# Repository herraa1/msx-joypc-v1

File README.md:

# PC gameport joystick controller adapter for MSX (msx-joypc) v1

Connect [PC gameport joysticks](https://en.wikipedia.org/wiki/Game_port) to [MSX computers](https://www.msx.org/wiki/).

> [!NOTE]
>
> No build instructions are yet provided, but if you are brave enough go for the [recommended build](#recommended-build).
>

## Introduction

The msx-joypc v1 is an adapter that allows connecting PC gameport joysticks to [MSX general purpose I/O ports](https://www.msx.org/wiki/General_Purpose_port).

The main features of the msx-joypc v1 adapter are:
* small footprint
* made of widely available electronic components
* behaves as a cord extension between the MSX computer and the PC gameport joystick
* uses a female standard DE9 connector on the adapter's MSX joystick side
* uses a [DA-15](https://en.wikipedia.org/wiki/D-subminiature) socket on the adapter's PC gameport joystick side
* no need for external power supply, the adapter draws current from the MSX port
* low power consumption (<20mA)
* serial debug provides information about the operation of the adapter

## [Hardware](hardware/kicad/)

The msx-joypc v1 adapter uses an [Atmega328p](https://en.wikipedia.org/wiki/ATmega328) to convert the [PC gameport joystick signalling](https://www.epanorama.net/documents/joystick/pc_joystick.html) to the [MSX joystick standard signalling](https://www.msx.org/wiki/Joystick_control).

A two-sided printed circuit board (PCB) is used to put together all components:
* An Atmega328p as the main MCU, running at 5V 16MHz
* Two 74LS03 quad 2-input NAND gates with open collectors to completely mimic the standard MSX joystick behavior
* A PTC fuse to minimize damage to the MSX computer in case something goes wrong with the board
* Several additional required components (crystal, diode, leds, resistors, ceramic capacitors and a tantalum capacitor)
* An angled DA-15 socket is used to directly connect the PC gameport joystick
* A PH2.0 connector is used to connect the MSX cable extension
* A 2.54 pitch debug header is added for serial debug and programming
* An ICSP header is provided for burning a bootloader or to flash the chip using a hardware programmer
* A DIP switch to configure the adapter for compatibility with different PC joysticks

Connection to the MSX general purpose I/O port is implemented using a DE9 joystick extension cable with a female DE9 connector on one side and a loose end on the other side.
The MSX joystick extension cable loose end is wired according to the following pinout mapping.

|  |
|:--|
| MSX joystick connector pinout, from controller plug side |

| MSX side pin | Cable color (may vary) | Signal |
| ------------ | ---------------------- | ------ |
| 5            | Brown                  | +5v    |
| 4            | Orange                 | RIGHT  |
| 3            | Grey                   | LEFT   |
| 2            | Black                  | DOWN   |
| 1            | Red                    | UP     |
| 6            | Green                  | TRIGA  |
| 7            | White                  | TRIGB  |
| 8            | Blue                   | OUT    |
| 9            | Yellow                 | GND    |

The msx-joypc v1 is fully compatible with MSX joysticks and honors the pin8 (OUT) signal.

The adapter uses open collector outputs (using 74LS03 Quad 2-Input NAND gates with open collector outputs) which makes the adapter safer [^2] than the
standard MSX joystick schematic depicted in the MSX Technical Data Book, as it avoids a series of undesired conditions that can lead to bus contention/short circuits.

Power is drawn from the +5V signal of the MSX general purpose I/O port, which is capable of delivering up to 50mA [^1].
The msx-joypc v1 draws below 20mA from the port when a controller is connected, so it is on the safe side. Anyway, the msx-joypc adapter uses a Positive Temperature Coeficient (PTC) resettable fuse of 50mA (F1) to limit current in case something goes wrong.

Also on the power side, a [1N5819 Schottky diode](https://www.diodes.com/assets/Datasheets/1N5819HW.pdf) (D1) is used to avoid leaking current from the msx-joypc adapter to the MSX in case power is applied to one of the VCC pins available on the ICSP or Debug headers while the adapter is plugged into an MSX.

Connection to the PC gameport joystick is done via a PC gameport joystick socket.

|  |
|:--|
| Gameport connector pinout, from PC gameport joystick side |

| Gameport pin   | Signal       | Comment                                                                   |
| -------------- | -------------| ------------------------------------------------------------------------- |
| 1              | +5V          | +5V power                                                                 |
| 2              | B1           | Button1                                                                   |
| 3              | X1           | Joystick 1 - X axis                                                       |
| 4              | GND          | ground                                                                    |
| 5              | GND          | ground                                                                    |
| 6              | Y1           | Joystick 1 - Y axis                                                       |
| 7              | B2           | Button2                                                                   |
| 8              | +5V          | +5V power                                                                 |
| 9              | +5V          | +5V power                                                                 |
| 10             | B3           | Button3                                                                   |
| 11             | X2           | Joystick 2 - X axis                                                       |
| 12             | GND/MIDI_OUT | ground / MIDI out                                                         |
| 13             | Y2           | Joystick 2 - Y axis                                                       |
| 14             | B4           | Button4                                                                   |
| 15             | +5V/MIDI_IN  | +5V power / MIDI_IN                                                       |

The PC gameport joystick uses 5V for power and logic.

Power for the PC gameport joystick is provided by the MSX +5V rail.

### Recommended Build

Please, use [msx-joypc-v1 Build2](#build2) for making new boards.

### [Build2](hardware/kicad/msx-joypc-v1-build2)

[Bill Of Materials (BoM)](https://html-preview.github.io/?url=https://raw.githubusercontent.com/herraa1/msx-joypc-v1/main/hardware/kicad/msx-joypc-v1-build2/bom/ibom.html)

This build fixes the following errata:
- make the ICSP header work again
- add (optional) RN1 and RN2 4k7 pull-downs to joystick signals to avoid spurious button joystick actions while powering up

This board has been successfully built and works fine.

### Build1

> [!WARNING]
> This build is broken. I messed up the ICSP header after a last-minute pin reordering. Meh.
> It can be fixed by cutting two traces, exposing two traces and using a pair of jumper wires to bridge the necessary points.
>
> Do NOT build. Use the [recommended build](#recommended-build) instead.
>

## [Firmware](firmware/msx-joypc-v1/)

The msx-joypc v1 adapter firmware uses a slightly modified version of [Necroware's GamePort adapter firmware](https://github.com/necroware/gameport-adapter) to read the PC gameport joystick status.

The following elements are used as inputs:
* joystick X and Y axis as direction arrows
* button 1, as Trigger 1
* button 2, as Trigger 2

Those elements' status are processed by the msx-joypc firmware and transformed into MSX general purpose I/O port's signals on the fly.

## [Enclosure](enclosure/)

### Acrylic

A simple acrylic enclosure design for the project is provided to protect the electronic components and provide strain relief for the extension cord.

The enclosure uses a 3mm acrylic sheet.

## Configuration Switches

Joystick Model               | Buttons | Axes  |  Hat | SW1-4 | Protocol   | Comments
-----------------------------|---------|-------|------|-------|------------|------------------------------------
Generic Analog               | 2       | 2     | 0    | 0000  | Analogue   |
Generic Analog               | 4       | 2     | 0    | 1000  | Analogue   |
Generic Analog               | 4       | 3     | 0    | 0100  | Analogue   | 3rd Axis is throttle
Generic Analog               | 4       | 4     | 0    | 1100  | Analogue   |
CH FlightStick               | 4       | 4     | 1    | 0010  | Analogue   |
CH F16 Combat Stick          | 10      | 3     | 1    | 0110  | Analogue   |
ThrustMaster                 | 4       | 3     | 1    | 1010  | Analogue   |
Sidewinder GamePad           | 10      | 2     | 0    | 1110  | Sidewinder |
Sidewinder 3D Pro            | 8       | 4     | 1    | 1110  | Sidewinder |
Sidewinder 3D Pro Plus       | 9       | 4     | 1    | 1110  | Sidewinder | First version of Precision Pro
Sidewinder Precision Pro     | 9       | 4     | 1    | 1110  | Sidewinder |
Sidewinder FFB Pro           | 9       | 4     | 1    | 1110  | Sidewinder | FFB not yet implemented
Sidewinder FFB Wheel         | 8       | 3     | 0    | 1110  | Sidewinder | FFB not yet implemented
Gravis GamePad Pro           | 10      | 2     | 0    | 0001  | GrIP       |
Logitech WingMan Extreme     | 6       | 3     | 1    | 1001  | ADI        |
Logitech CyberMan 2          | 8       | 6     | 0    | 1001  | ADI        |
Logitech WingMan Interceptor | 9       | 3     | 3    | 1001  | ADI        | 2 hats are mapped as 4 axes
Logitech ThunderPad Digital  | 8       | 2     | 0    | 1001  | ADI        | Directional buttons mapped as 2 axes
Logitech WingMan Gamepad     | 11      | 2     | 0    | 1001  | ADI        | Directional buttons mapped as 2 axes
Logitech WingMan Light       | 2       | 2     | 0    | 0000  | Analogue   |

For an up to date information see [Which joysticks does this adapter support](https://github.com/necroware/gameport-adapter?tab=readme-ov-file#which-joysticks-does-this-adapter-support) on [Necroware's GamePort adapter project](https://github.com/necroware/gameport-adapter).

## LED indicators

| **LED**   | **State**      | **Indication** |
|-----------|----------------|---------------|
| _POWER_   | Off            | board is not receiving 5V power |
| _POWER_   | Solid Red      | board is receiving 5V power     |
| _JoyPort_ | Off            | no PC joystick connected or recognized |
| _JoyPort_ | Solid Green    | PC joystick connected and ready to use |

## References

MSX general purpose I/O port
* https://www.msx.org/wiki/General_Purpose_port

Atmega328p pinout
- https://camo.githubusercontent.com/06bc0a6bb71729956af107f56c3e57bd065d9fb924bcc7f6bb8fbb487a1a5e55/68747470733a2f2f692e696d6775722e636f6d2f6e6177657145362e6a7067

Joystick PC Gameport pinout
* https://allpinouts.org/pinouts/connectors/input_device/joystick-pc-gameport/

PC joystick interface
* https://www.epanorama.net/documents/joystick/pc_joystick.html

Necroware's GamePort adapter project
* https://github.com/necroware/gameport-adapter

Using a PC Joystick with the Arduino
* http://www.built-to-spec.com/blog/2009/09/10/using-a-pc-joystick-with-the-arduino/

Arduino gameport interface
* https://build-its.blogspot.com/2012/01/arduino-game-port-interface.html

DIY gameport to USB adapter
* https://littlebigtech.net/posts/diy-gameport-to-usb-adapter/

## Image Sources

* https://www.oshwa.org/open-source-hardware-logo/
* https://en.wikipedia.org/wiki/File:Numbered_DE9_Diagram.svg

[^1]: https://www.msx.org/wiki/General_Purpose_port
[^2]: https://www.msx.org/wiki/Joystick/joypad_controller (see "Undesired Conditions")

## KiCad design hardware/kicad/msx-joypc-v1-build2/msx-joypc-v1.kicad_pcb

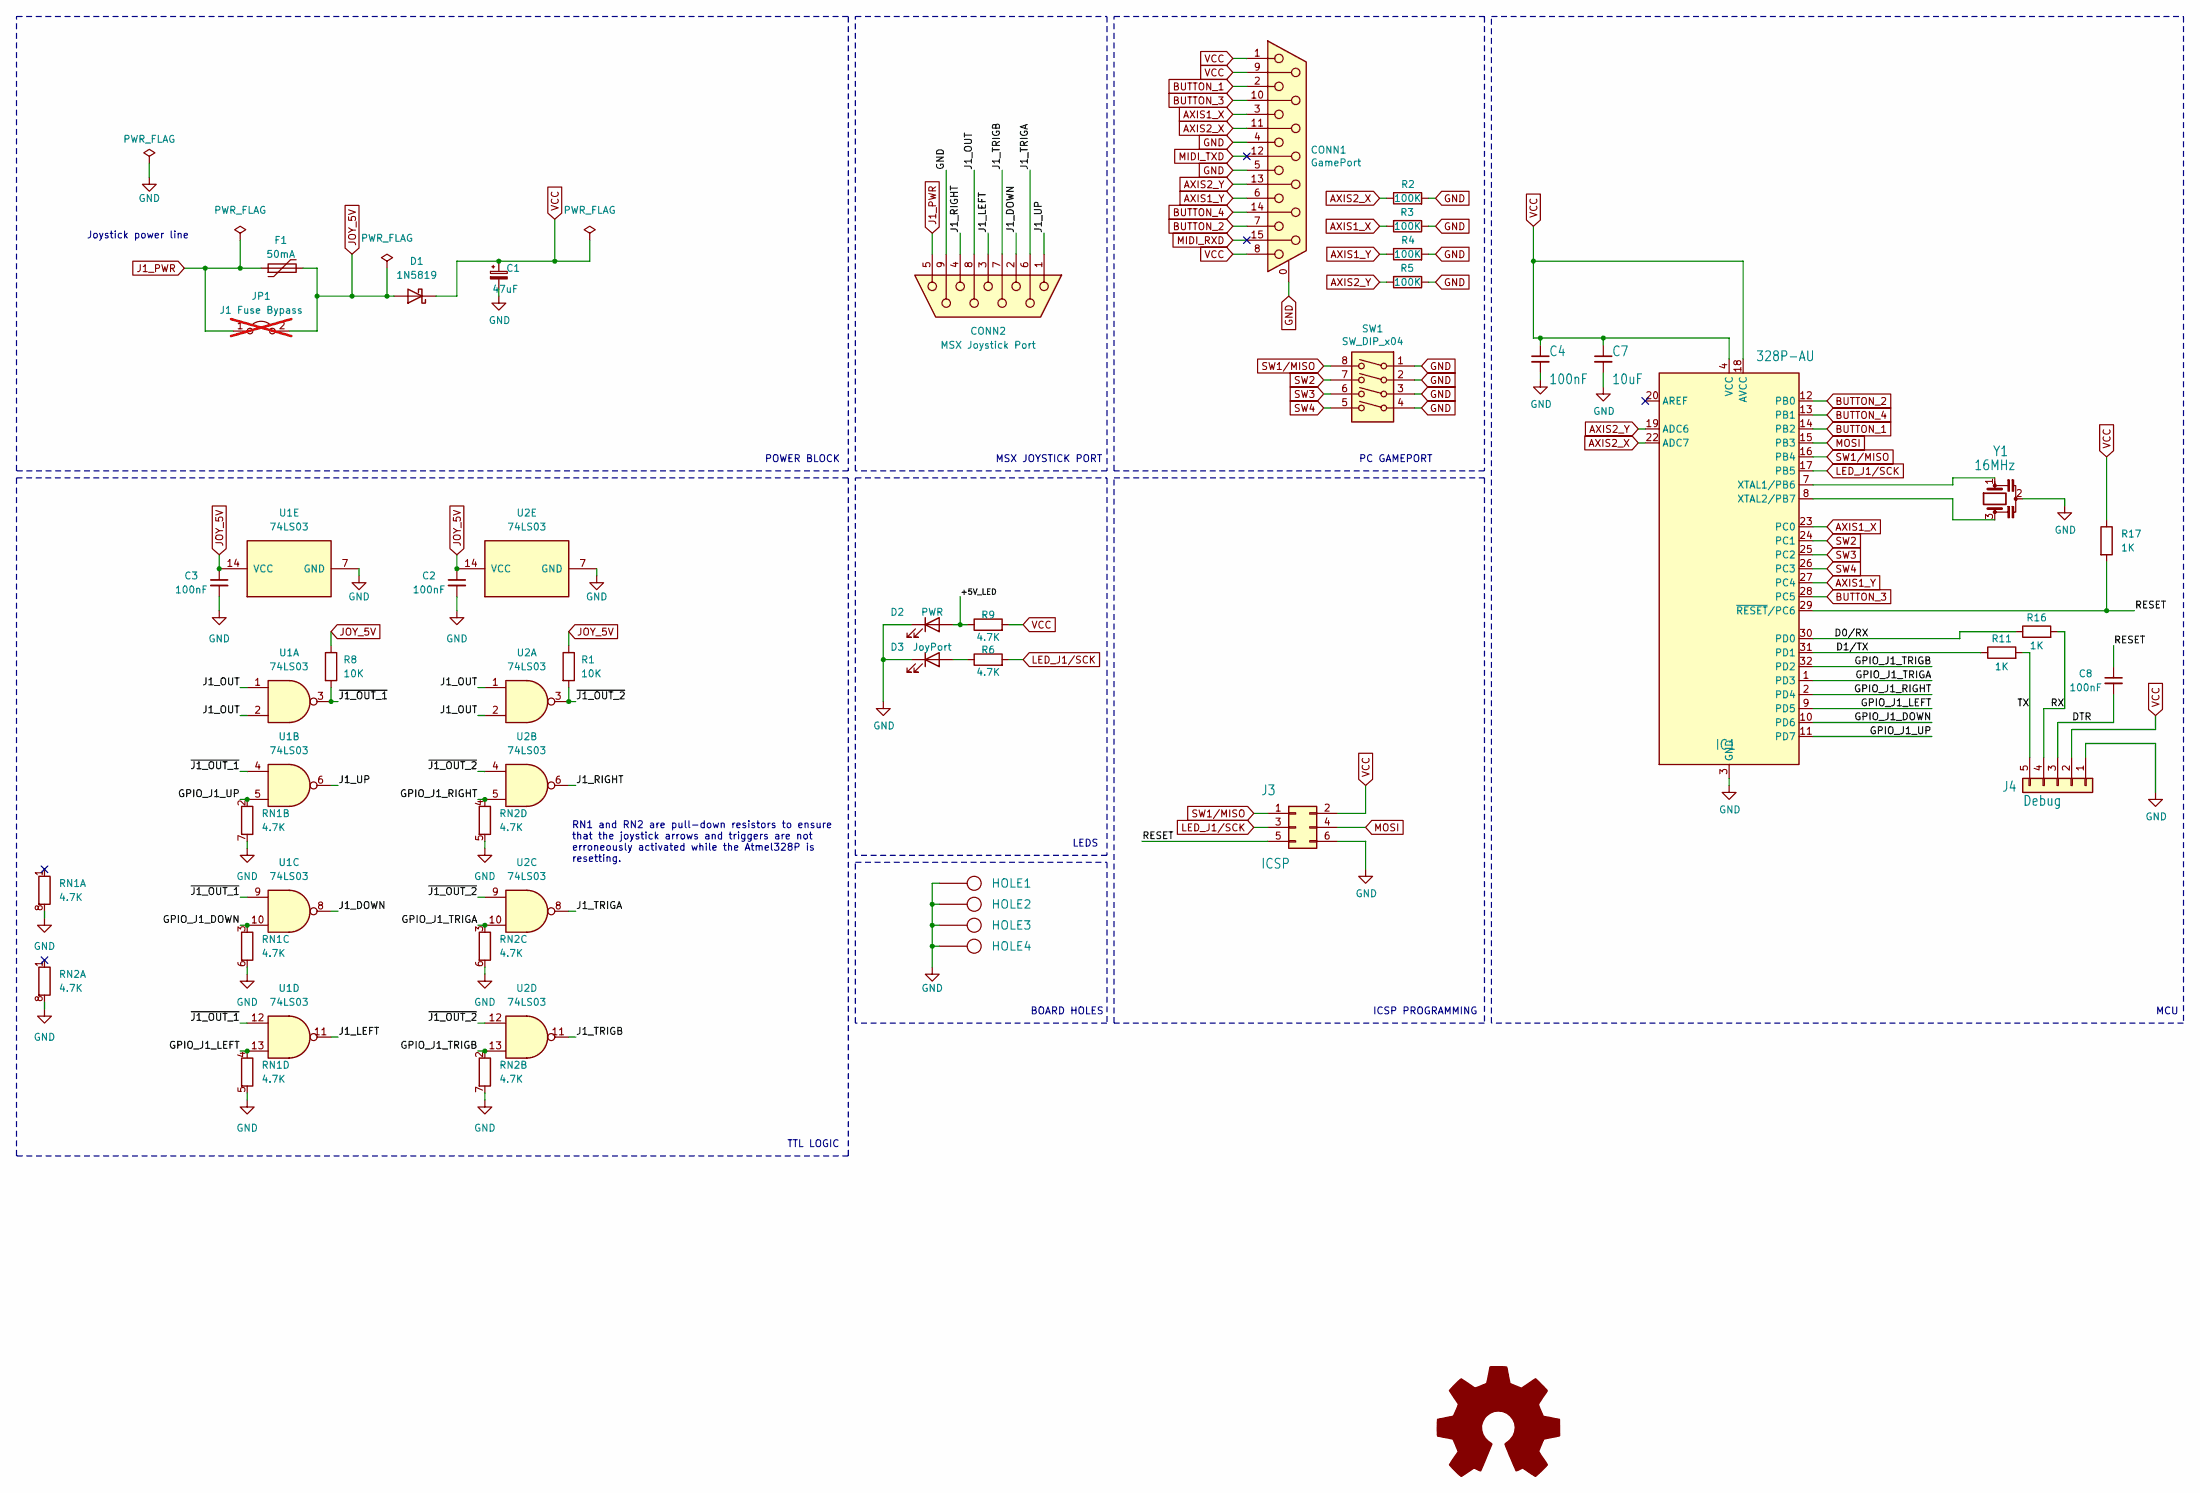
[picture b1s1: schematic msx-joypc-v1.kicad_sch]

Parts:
C1: 47uF; CP_EIA-3216-18_Kemet-A_Pad1.58x1.35mm_HandSolder
C2, C3, C4, C8: 100nF; C_0805_2012Metric_Pad1.18x1.45mm_HandSolder
C7: 10uF; C_0805_2012Metric_Pad1.18x1.45mm_HandSolder
CONN1: GamePort; DSUB-15_Female_Horizontal_P2.77x2.84mm_EdgePinOffset7.70mm_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; LCSC C77835
CONN2: MSX Joystick Port; JST_PH_B9B-PH-K_1x09_P2.00mm_Vertical
D1: 1N5819; D_SOD-123
D2: PWR; LED_0805_2012Metric_Pad1.15x1.40mm_HandSolder
D3: JoyPort; LED_0805_2012Metric_Pad1.15x1.40mm_HandSolder
F1: 50mA; Fuse_1206_3216Metric_Pad1.42x1.75mm_HandSolder
HOLE1, HOLE2, HOLE3, HOLE4: HOLE; Hole_3mm
IC1: 328P-AU; TQFP-32_7x7mm_P0.8mm
J3: ICSP; PinHeader_2x03_P2.54mm_Vertical
J4: Debug; PinHeader_1x05_P2.54mm_Vertical
JP1: J1 Fuse Bypass; PinHeader_1x02_P2.54mm_Vertical; not fitted
R1, R8: 10K; R_0805_2012Metric_Pad1.20x1.40mm_HandSolder
R2, R3, R4, R5: 100K; R_0805_2012Metric_Pad1.20x1.40mm_HandSolder; LCSC C172965
R6: 4.7K; R_0805_2012Metric_Pad1.20x1.40mm_HandSolder; LCSC C4310
R9: 4.7K; R_0805_2012Metric_Pad1.20x1.40mm_HandSolder
R11, R16, R17: 1K; R_0805_2012Metric_Pad1.20x1.40mm_HandSolder
RN1, RN2: 4.7K; R_Array_Concave_4x0603
SW1: SW_DIP_x04; SW_DIP_SPSTx04_Piano_10.8x11.72mm_W7.62mm_P2.54mm; LCSC C15781
SYM1: Logo_Open_Hardware_Large; OSHW-Logo_7.5x8mm_SilkScreen
U1, U2: 74LS03; SOIC-14_3.9x8.7mm_P1.27mm
Y1: 16MHz; Resonator_SMD_Murata_CSTxExxV-3Pin_3.0x1.1mm_HandSoldering

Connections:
/+5V_LED: D2.2 (A), R9.1
/D0/RX: IC1.30 (PD0), R16.1
/D1/TX: IC1.31 (PD1), R11.1
/DTR: C8.2, J4.3
/GPIO_J1_DOWN: IC1.10 (PD6), RN1.3 (R3.1), U1.10
/GPIO_J1_LEFT: IC1.9 (PD5), RN1.4 (R4.1), U1.13
/GPIO_J1_RIGHT: IC1.2 (PD4), RN2.4 (R4.1), U2.5
/GPIO_J1_TRIGA: IC1.1 (PD3), RN2.3 (R3.1), U2.10
/GPIO_J1_TRIGB: IC1.32 (PD2), RN2.2 (R2.1), U2.13
/GPIO_J1_UP: IC1.11 (PD7), RN1.2 (R2.1), U1.5
/J1_DOWN: CONN2.2, U1.8
/J1_LEFT: CONN2.3, U1.11
/J1_OUT: CONN2.8, U1.1, U1.2, U2.1, U2.2
/J1_RIGHT: CONN2.4, U2.6
/J1_TRIGA: CONN2.6, U2.8
/J1_TRIGB: CONN2.7, U2.11
/J1_UP: CONN2.1, U1.6
/RESET: C8.1, IC1.29 (~RESET/PC6), J3.5, R17.2
/RX: J4.4, R16.2
/TX: J4.5, R11.2
/~J1_OUT_1: R8.2, U1.3, U1.4, U1.9, U1.12
/~J1_OUT_2: R1.2, U2.3, U2.4, U2.9, U2.12
AXIS1_X: CONN1.3, IC1.23 (PC0), R3.2
AXIS1_Y: CONN1.6, IC1.27 (PC4), R4.1
AXIS2_X: CONN1.11 (P111), IC1.22 (ADC7), R2.1
AXIS2_Y: CONN1.13, IC1.19 (ADC6), R5.2
BUTTON_1: CONN1.2, IC1.14 (PB2)
BUTTON_2: CONN1.7, IC1.12 (PB0)
BUTTON_3: CONN1.10, IC1.28 (PC5)
BUTTON_4: CONN1.14, IC1.13 (PB1)
GND: C1.2, C2.2, C3.2, C4.2, C7.2, CONN1.0 (PAD), CONN1.4, CONN1.5, CONN2.9, D2.1 (K), D3.1 (K), HOLE1.1, HOLE2.1, HOLE3.1, HOLE4.1, IC1.3 (GND), IC1.5 (GND), IC1.21 (GND), J3.6, J4.1, R2.2, R3.1, R4.2, R5.1, RN1.5 (R4.2), RN1.6 (R3.2), RN1.7 (R2.2), RN1.8 (R1.2), RN2.5 (R4.2), RN2.6 (R3.2), RN2.7 (R2.2), RN2.8 (R1.2), SW1.1, SW1.2, SW1.3, SW1.4, U1.7 (GND), U2.7 (GND), Y1.2
J1_PWR: CONN2.5, F1.1, JP1.1 (A)
JOY_5V: C2.1, C3.1, D1.2 (A), F1.2, JP1.2 (B), R1.1, R8.1, U1.14 (VCC), U2.14 (VCC)
LED_J1/SCK: IC1.17 (PB5), J3.3, R6.2
MIDI_RXD: CONN1.15
MIDI_TXD: CONN1.12
MOSI: IC1.15 (PB3), J3.4
unnamed: D3.2 (A), R6.1
unnamed: IC1.7 (XTAL1/PB6), Y1.1
unnamed: IC1.8 (XTAL2/PB7), Y1.3
SW1/MISO: IC1.16 (PB4), J3.1, SW1.8
SW2: IC1.24 (PC1), SW1.7
SW3: IC1.25 (PC2), SW1.6
SW4: IC1.26 (PC3), SW1.5
VCC: C1.1, C4.1, C7.1, CONN1.1, CONN1.8, CONN1.9, D1.1 (K), IC1.4 (VCC), IC1.6 (VCC), IC1.18 (AVCC), J3.2, J4.2, R9.2, R17.1

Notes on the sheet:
MCU
LEDS
MSX JOYSTICK PORT
TTL LOGIC
BOARD HOLES
Joystick power line
ICSP PROGRAMMING
RN1 and RN2 are pull-down resistors to ensure that the joystick arrows and triggers are not erroneously activated while the Atmel328P is resetting.
PC GAMEPORT
POWER BLOCK

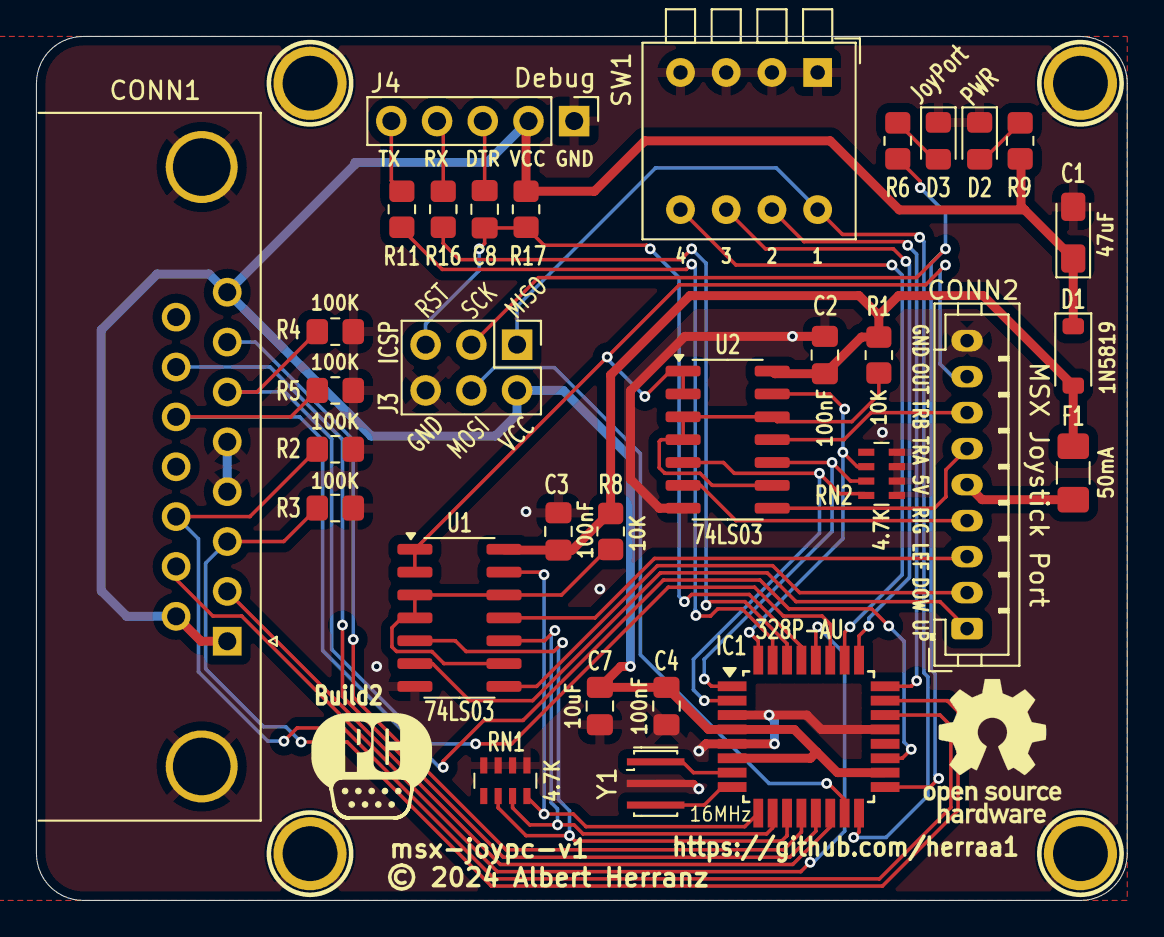
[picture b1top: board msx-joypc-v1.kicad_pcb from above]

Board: 2 copper layers, 60.6 x 48.0 mm, 37 parts (0 on the bottom side), 43 nets.

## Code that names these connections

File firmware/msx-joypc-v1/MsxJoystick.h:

/*
 * msx-joypc v1, a PC gameport to MSX joystick adapter
 * Copyright (C) 2024 Albert Herranz
 *
 * This code is released under GPL V2.0
 *
 * Valid-License-Identifier: GPL-2.0-only
 * SPDX-URL: https://spdx.org/licenses/GPL-2.0-only.html
 *
 */
//
// Based on Necroware's GamePort adapter firmware.
// Copyright (C) 2021 Necroware
//
// This program is free software: you can redistribute it and/or modify
// it under the terms of the GNU General Public License as published by
// the Free Software Foundation, either version 3 of the License, or
// (at your option) any later version.
//
// This program is distributed in the hope that it will be useful,
// but WITHOUT ANY WARRANTY; without even the implied warranty of
// MERCHANTABILITY or FITNESS FOR A PARTICULAR PURPOSE.  See the
// GNU General Public License for more details.
//
// You should have received a copy of the GNU General Public License
// along with this program. If not, see <https://www.gnu.org/licenses/>.

#pragma once

#include "Buffer.h"
#include "Joystick.h"
#include "Utilities.h"
#include <Arduino.h>

#include "DigitalPin.h"
#include <avr/wdt.h>

void __force_system_reset(void) {
	MCUSR = 0;
	wdt_enable(WDTO_250MS);
	while(1)  ;  // force WDT to reset system
}

class MsxJoystick {
public:
  bool init(Joystick *joystick) {
    
    if (!joystick || !joystick->init()) {
      return false;
    }

    m_joystick = joystick;
    m_state = State::BOOT_CONNECTED_CONNECTED;
    m_led.setHigh();

    const auto &desc = m_joystick->getDescription();
    log("Configured device: %s (%d axes, %d buttons)", desc.name, desc.numAxes, desc.numButtons);

    return true;
  }

  bool update() {
    if (!m_joystick || !m_joystick->update()) {
      return false;
    }

    const auto &state = m_joystick->getState();
    const auto &desc = m_joystick->getDescription();

#ifdef DIAG
    static auto last_state = m_joystick->getState();

    for (auto i = 0u; i < desc.numAxes; i++) {
        log_nolf("axes[%d] = %d,", i, state.axes[i]);
    }

    if (desc.hasHat) {
      if (last_state.hat != state.hat) {
        log_nolf("hat = %d,", state.hat);
      }
    }

    if (desc.numButtons) {
      if (last_state.buttons != state.buttons) {
        log_nolf("buttons = %d", state.buttons);
      }
    }
    log_nolf("\n");

    last_state = state;
#endif

    int16_t lx, ly;

    ly = (1 < desc.numAxes)?state.axes[1]:s_axis_threshold_min;
    lx = (0 < desc.numAxes)?state.axes[0]:s_axis_threshold_min;

    if (lx == 1023 && ly == 1023) {
        switch(m_state) {
            case State::BOOT_CONNECTED_CONNECTED:
                m_state = State::BOOT_CONNECTED_UNCONNECTED_MAYBE;
                m_last_state_millis = millis();
                break;
            case State::BOOT_CONNECTED_UNCONNECTED_MAYBE:
                unsigned long current_millis = millis();
                if (current_millis - m_last_state_millis >= s_joystick_dead_time) {
                    // adapter started with joystick connected, but joystick was disconnected
                    m_state = State::BOOT_CONNECTED_UNCONNECTED_CONFIRMED;
                    m_last_state_millis = millis();
                    log("Adapter booted with joystick connected, but now joystick is disconnected");
                    m_led.setLow();
                }
                break;
        }
    } else if (lx == 511 && ly == 511) {
        switch(m_state) {
            case State::BOOT_CONNECTED_CONNECTED:
                m_state = State::BOOT_UNCONNECTED_UNCONNECTED_MAYBE;
                m_last_state_millis = millis();
                break;
            case State::BOOT_UNCONNECTED_UNCONNECTED_MAYBE:
                unsigned long current_millis = millis();
                if (current_millis - m_last_state_millis >= s_joystick_dead_time) {
                    // adapter started with joystick not connected, joystick still disconnected
                    m_state = State::BOOT_UNCONNECTED_UNCONNECTED_CONFIRMED;
                    m_last_state_millis = millis();
                    log("Adapter booted with joystick disconnected");
                    m_led.setLow();
                    __update_msx_signals(0);
                }
                break;
        }
    } else {
        switch(m_state) {
            case State::BOOT_CONNECTED_UNCONNECTED_CONFIRMED:
                // fallthrough
            case State::BOOT_UNCONNECTED_UNCONNECTED_CONFIRMED:
                log("Joystick reconnected, restarting adapter!");
                delay(5);
                __force_system_reset();
                break;
        }
        m_state = State::BOOT_CONNECTED_CONNECTED;
    }

    uint8_t joystick_signals = 0x00;

    if (m_state != State::BOOT_CONNECTED_UNCONNECTED_CONFIRMED && m_state != State::BOOT_UNCONNECTED_UNCONNECTED_CONFIRMED) {
        if ((state.buttons & 0x01) || (state.buttons & 0x04))
            joystick_signals |= (1 << MsxPortPins::MSX_JOYSTICK_TRIGGER1);

        if ((state.buttons & 0x02) || (state.buttons & 0x08))
            joystick_signals |= (1 << MsxPortPins::MSX_JOYSTICK_TRIGGER2);

        if ((ly > s_axis_threshold_max) && !(joystick_signals & (1 << MsxPortPins::MSX_JOYSTICK_UP)))
            joystick_signals |= (1 << MsxPortPins::MSX_JOYSTICK_DOWN);

        /* before activating UP check that DOWN is not activated */
        if ((ly < s_axis_threshold_min) && !(joystick_signals & (1 << MsxPortPins::MSX_JOYSTICK_DOWN)))
            joystick_signals |= (1 << MsxPortPins::MSX_JOYSTICK_UP);

        /* before activating LEFT check that RIGHT is not activated */
        if ((lx < s_axis_threshold_min) && !(joystick_signals & (1 << MsxPortPins::MSX_JOYSTICK_RIGHT)))
            joystick_signals |= (1 << MsxPortPins::MSX_JOYSTICK_LEFT);

        /* before activating RIGHT check that LEFT is not activated */
        if ((lx > s_axis_threshold_max) && !(joystick_signals & (1 << MsxPortPins::MSX_JOYSTICK_LEFT)))
            joystick_signals |= (1 << MsxPortPins::MSX_JOYSTICK_RIGHT);
    }

    __update_msx_signals(joystick_signals);

    return true;
  }

private:
  static constexpr unsigned long s_joystick_dead_time = 2UL * 1000UL; // 2 seconds
  static constexpr auto s_axis_threshold = (1023 - 0) / 3;
  static constexpr auto s_axis_threshold_min = 0 + s_axis_threshold;
  static constexpr auto s_axis_threshold_max = 1023 - s_axis_threshold;

  Joystick *m_joystick{};
  DigitalOutput<13> m_led;

  enum class State {
    BOOT_CONNECTED_CONNECTED,
    BOOT_CONNECTED_UNCONNECTED_MAYBE,
    BOOT_CONNECTED_UNCONNECTED_CONFIRMED,
    BOOT_UNCONNECTED_UNCONNECTED_MAYBE,
    BOOT_UNCONNECTED_UNCONNECTED_CONFIRMED
  };

  unsigned long m_last_state_millis;
  State m_state;

#define PORT_MSX_JOYSTICK PORTD
#define DDR_MSX_JOYSTICK  DDRD

  enum MsxPortPins {
    /* MSX general purpose signals as mapped to Atmega328p PORTD bits */
    MSX_JOYSTICK_UP = 7,       /* PD7, MSX joystick pin1 */
    MSX_JOYSTICK_DOWN = 6,     /* PD6, MSX joystick pin2 */
    MSX_JOYSTICK_LEFT = 5,     /* PD5, MSX joystick pin3 */
    MSX_JOYSTICK_RIGHT = 4,    /* PD4, MSX joystick pin4 */
    MSX_JOYSTICK_TRIGGER1 = 3, /* PD3, MSX joystick pin6 */
    MSX_JOYSTICK_TRIGGER2 = 2, /* PD2, MSX joystick pin7 */
  };

  static constexpr bool direct_mode = false; // direct_mode uses open collector outputs (use only in test prototype without 74LS03)

  static inline void __update_msx_signals(uint8_t signals)
  {
    /* write all signal states at once to MSX side */
    if (direct_mode) {
        PORT_MSX_JOYSTICK = ~signals;
        DDR_MSX_JOYSTICK = signals;
    } else {
        PORT_MSX_JOYSTICK = signals;
        DDR_MSX_JOYSTICK = ~0;
    }
  }

};

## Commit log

2024-11-02 Initialize repository.
2024-11-03 Initial commit.
2024-11-03 readme: fix wrong link and remove unexisting (yet) image
2024-11-03 readme: added kiCanvas link to build1
2024-11-09 readme: mark build1 as broken
2024-11-09 firmware: fix reset loop when bootloader that does not disable the watchdog
2024-11-10 readme: some re-wording, add fix images for build1
2024-12-14 firmware: improve hotplug, cosmetics
2024-12-14 kicad: add build2
2024-12-14 readme: update, add information for build2
2024-12-20 readme: update enclosure info, document leds and switches
2024-12-20 readme: change notice to github markup note

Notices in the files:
hardware/kicad/msx-joypc-v1-build2/msx-joypc-v1.kicad_pcb:
© 2024 Albert Herranz
